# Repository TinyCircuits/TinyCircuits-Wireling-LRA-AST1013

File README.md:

# TinyCircuits Wireling LRA
# AST1013 Rev1

The design files are located under design_files/ for the TinyCircuits AST1013 Rev 1 PCB. This is a Wireling board which features the TI DRV2605 Haptic Linear Resonant Actuator driver (also known as a fancy vibration motor), including built in TouchSense2200 software comprising over 100 pre-created effects.

Format is in Cadsoft Eagle format - Eagle version 6.2 was used for the original design.

For more infomation on this, check out the product page at TinyCircuits.com

# License:

Design by TinyCircuits.
All design files are released under the Creative Commons Attribution Share-Alike 3.0 License, see the following link for details: http://creativecommons.org/licenses/by-sa/3.0

All text above must be included in any redistribution or derived design

This project uses designs and concepts developed as part of the Arduino project and the LilyPad project.  The TinyCircuits design files themselves (schematics, PCB and libraries) are not directly derived from these works' design files and have been created new, however the concepts and basic architecture behind the TinyDuino and TinyLily products are derived and we thank the hard work of the organizations below for their contributions to open-source hardware:
  
Original Arduino Uno Design by Team Arduino

LilyPad Arduino Design by Leah Buechley and Sparkfun Electronics

Please support the open-source hardware community

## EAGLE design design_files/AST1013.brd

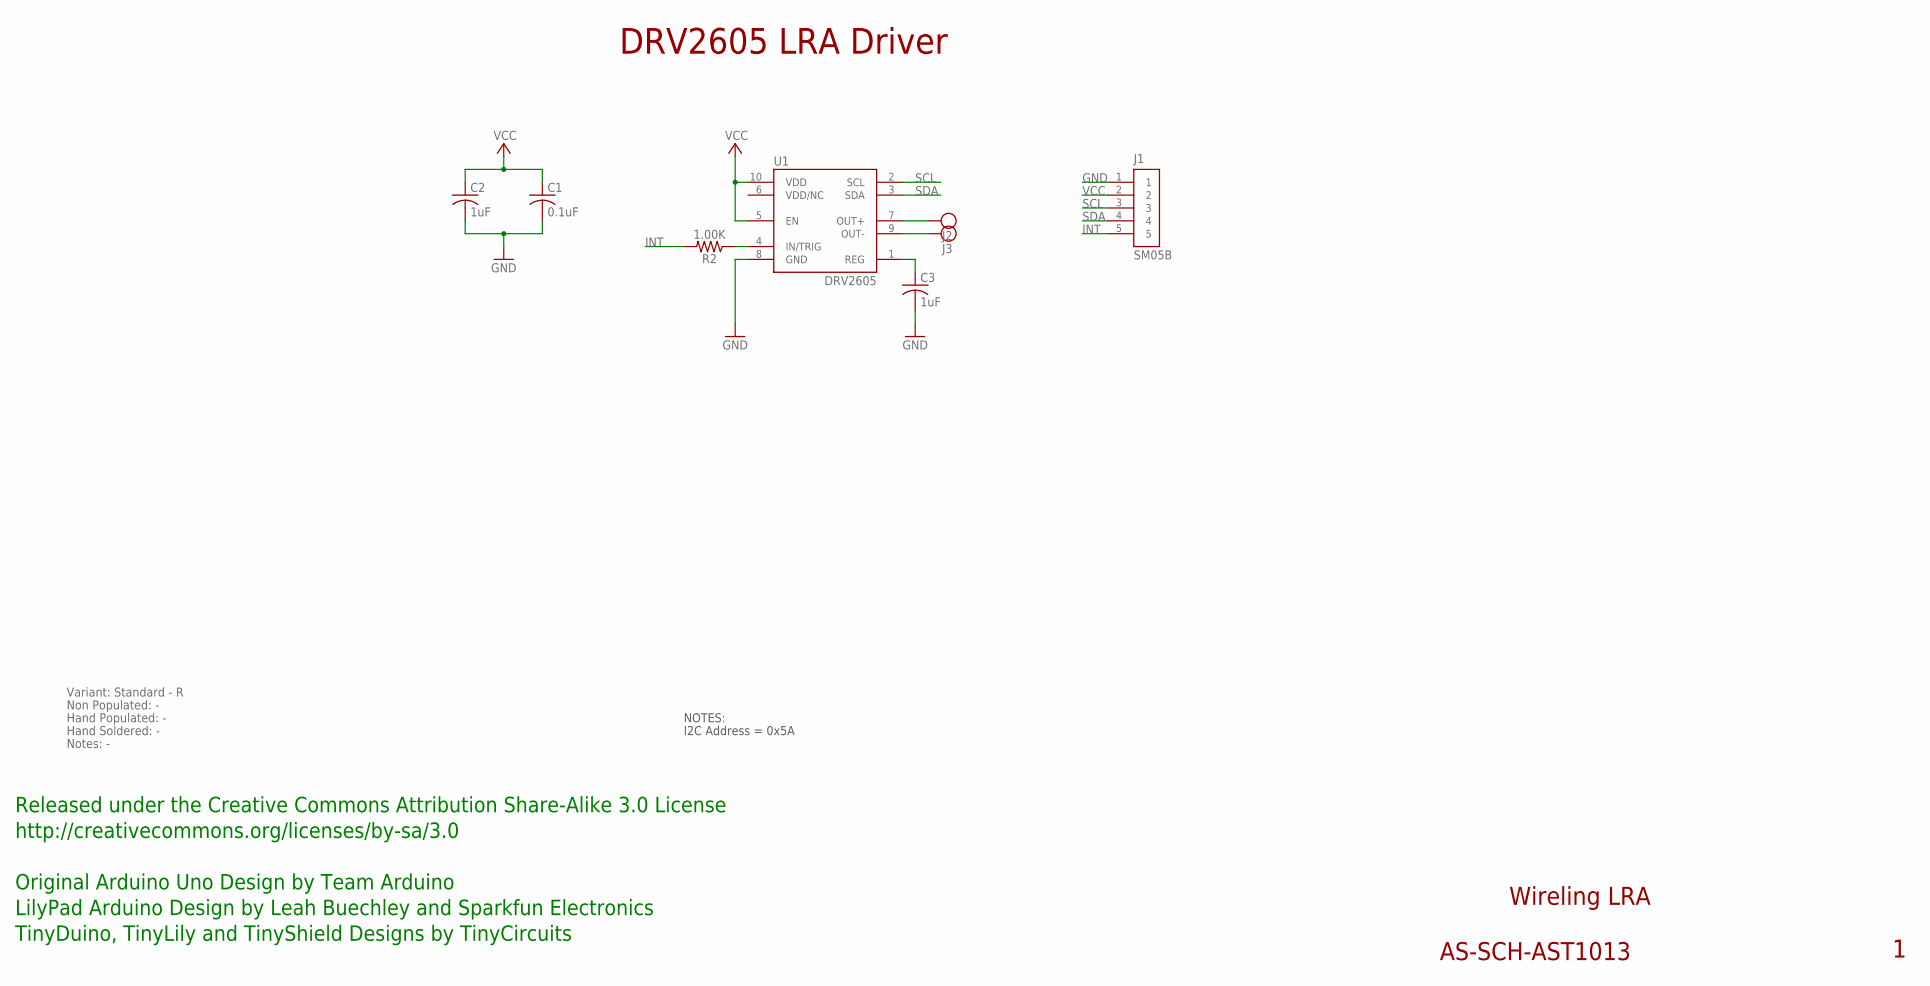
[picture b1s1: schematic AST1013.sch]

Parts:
C1: 0.1uF; C0402
C2: 1uF; C0603; PARTNO AS-ITM-00410
C3: 1uF; C0402
J1: SM05B; JST_SH_5X1
J2, J3: PIN_1X.1"1; 1X.1"_2
R2: 1.00K; 0402; PARTNO AS-ITM-00003
U1: DRV2605; DGS(S-PDSO-G10)

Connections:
GND: C1.2, C2.2, C3.2, J1.1, U1.8 (GND)
INT: J1.5, R2.2
unnamed: J2.1, U1.7 (OUT+)
unnamed: J3.1, U1.9 (OUT-)
unnamed: C3.1, U1.1 (REG)
unnamed: R2.1, U1.4 (IN/TRIG)
SCL: J1.3, U1.2 (SCL)
SDA: J1.4, U1.3 (SDA)
VCC: C1.1, C2.1, J1.2, U1.5 (EN), U1.10 (VDD)

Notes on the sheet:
Wireling LRA
AS-SCH-AST1013
DRV2605 LRA Driver
Released under the Creative Commons Attribution Share-Alike 3.0 License
http://creativecommons.org/licenses/by-sa/3.0
Original Arduino Uno Design by Team Arduino
TinyDuino, TinyLily and TinyShield Designs by TinyCircuits
LilyPad Arduino Design by Leah Buechley and Sparkfun Electronics
Non Populated: -
Hand Populated: -
Hand Soldered: -
Variant: Standard - R
Notes: -
NOTES:
I2C Address = 0x5A

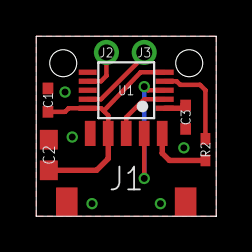
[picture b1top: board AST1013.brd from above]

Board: 2 copper layers, 10.0 x 10.0 mm, 9 parts (0 on the bottom side), 9 nets.

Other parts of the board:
U$1: DOCFIELD-TINYCIRCUITS-PCB

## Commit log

2019-08-02 added datasheet
2019-09-30 fix program
2019-09-30 fix program, round 2
2019-10-28 update name
2019-11-25 update program
2019-12-30 added image
2020-01-10 oops
2020-01-10 remove
2020-02-04 mass image update
2020-08-14 Add CAD data
